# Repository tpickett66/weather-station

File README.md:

# Weather Station

This project has two purposes, the first and primary purpose is to build a small device that can be deployed to gather
and optionally display atmospheric temperature, humidity, and barometric pressure both indoors and out. The second
purpose is to serve as a simple test-bed for microcontroller platforms, wireless connectivity solutions, and software
development options. To get started quickly I'm using an ESP32 communicating over WiFi leveraging the Arduino framework,
both the ESP32 and WiFi are way more power hungry than would be ideal for a battery powered version but for indoor use
with wall power it will be fine.

## Microcontrollers to try
These options represent a few different families of technology, some will be much lower power than the base ESP32 while
others will be about the same.

* ESP32-C3 (Risc-V single core)
* STM32 line (probably the F0)
* ???

## Wireless technologies to explore
WiFi is great for when a ton of bandwidth is needed and the requisite power is available. Eventually I would like to
build a solar-powered version of this I can stick out in the yard or even in the forest so a less power hungry, 
longer-range solution will be nice to have.

* LoRa
* Zigbee
* Thread

## Licensing
As of right now the code is licensed under the LGPL since that's what the ESP32's Arduino stack is licensed under, if
another framework is used for other implementations the licensing will probably be changed to something less restrictive
of derivative works.

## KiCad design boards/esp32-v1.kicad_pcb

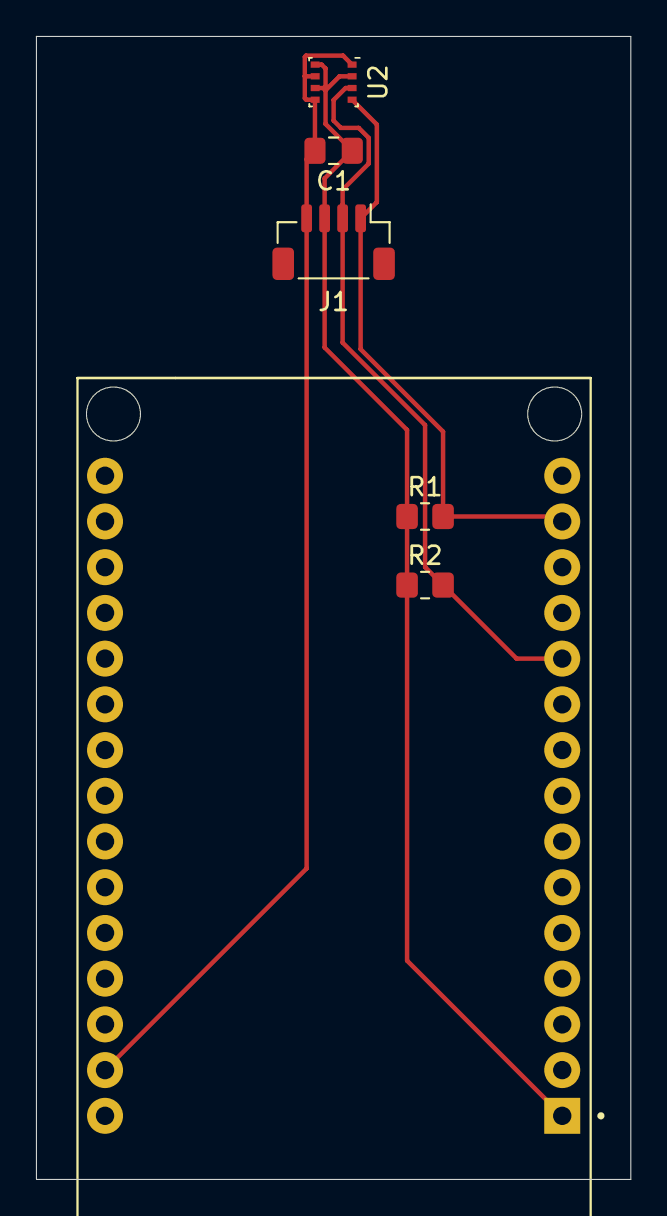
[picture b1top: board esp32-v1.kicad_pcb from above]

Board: 2 copper layers, 33.0 x 63.5 mm, 6 parts (0 on the bottom side), 4 nets.

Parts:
C1: 200n; C_0805_2012Metric_Pad1.18x1.45mm_HandSolder
J1: Conn_01x04_Male; JST_SH_BM04B-SRSS-TB_1x04-1MP_P1.00mm_Vertical
R1, R2: 4.7k; R_0805_2012Metric_Pad1.20x1.40mm_HandSolder
U1: ESP32-DEVKIT-V1; MODULE_ESP32_DEVKIT_V1
U2: BME280; Bosch_LGA-8_2.5x2.5mm_P0.65mm_ClockwisePinNumbering

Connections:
+3V3: C1.1, J1.3, R1.1, R2.1, U1.1, U2.2, U2.6, U2.8
GND: C1.2, J1.4, U1.2, U1.29, U2.1, U2.5, U2.7
SCL: J1.1, R1.2, U1.14, U2.4
SDA: J1.2, R2.2, U1.11, U2.3

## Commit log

2021-09-25 Pio Generator and display init
2021-09-25 Read measurements from BME280 and display them on the screen.
2021-10-02 re-init platformio to get libraries picked up correctly
    Yay for no more jank includes
2021-10-09 Stop using a delay to figure out when to take a reading
    Rather than delay() we're going to check if enough time has elapsed
    between readings, this will allow us to do other things between
    readings.
2021-10-14 Start implementing a preferences store and serial console to set them
2021-10-17 Implement help and reset commands for serial console
2021-10-17 Make timeouts wraparound safe
    The return value from millis() wraps around every 50ish days, during the
    wraparound we would get weirdness from the serial console and we'd get
    tons of sensor readings for a few seconds during wraparound. Neither of
    these conditions would be fatal but are easily avoided.
2021-10-30 Implement storing SSID through preferences
2021-11-03 Finish configuring and connecting to WiFi
2021-11-14 Set Hostname for WiFi network and make it actually work
2021-11-17 Add note to unsuckify the SerialConsole state machine
    What I'm doing works for now but if it gets much more functionality it
    will really suck to maintain, make it better before that happens.
2021-11-17 Add LICENSE file
    Since the arduino-esp32 is LGPL licensed so must this code be. I'll
    eventually add file headers.
2021-11-22 Add a sparse readme
2021-12-02 Initial pass at ESP32 board
    After laying this out it seems a bit silly to get a board manufactured
    for this. I may end up sticking with the little breakout boards a bit
    longer and figure out a better way to make the connections I need in a
    more permanent manner.
2021-12-02 Eliminate malloc/free in SerialConsole
    This wasn't really necessary but I wanted to see how far I could push
    things with stack-only allocations. Technically this probably ends up
    using a bit more memory since we're over allocating but it's fine.
2021-12-09 Configure and start the NTP service
    We'll need to attach timestamps with our temperature messages.
2021-12-09 Add configuration storage for MQTT host
2021-12-09 run cargo generator from the rust embedded tutorial
2021-12-09 Tweak things for the F0 we're using instead of the F3
